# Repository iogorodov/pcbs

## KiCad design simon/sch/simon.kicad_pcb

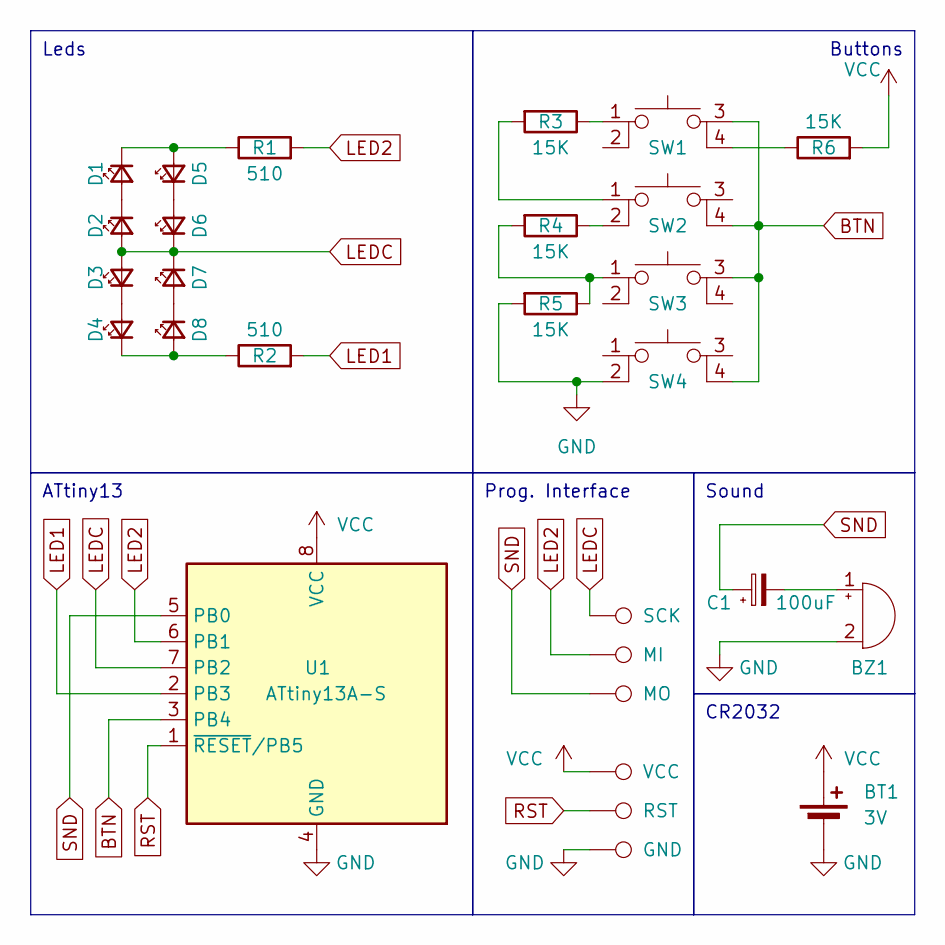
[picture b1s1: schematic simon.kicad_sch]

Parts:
BT1: 3V; BatteryHolder_KLS5_CR2032_02
BZ1: Buzzer; MagneticBuzzer_Kingstate_KCG0601
C1: 100uF; CP_Radial_D6.3mm_P2.50mm
D1, D2, D3, D4, D5, D6, D7, D8: LED_Small; LED_1206_3216Metric
R1, R2: 510; R_Axial_DIN0207_L6.3mm_D2.5mm_P7.62mm_Horizontal
R3, R4, R5, R6: 15K; R_Axial_DIN0207_L6.3mm_D2.5mm_P7.62mm_Horizontal
SW1, SW2, SW3, SW4: SW_Push_6x6mm
TP1: GND; TestPoint_Pad_D1.5mm
TP2: RST; TestPoint_Pad_D1.5mm
TP3: VCC; TestPoint_Pad_D1.5mm
TP4: SCK; TestPoint_Pad_D1.5mm
TP5: MI; TestPoint_Pad_D1.5mm
TP6: MO; TestPoint_Pad_D1.5mm
U1: ATtiny13A-S; SOIC-8W_5.3x5.3mm_P1.27mm

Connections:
BTN: SW1.3, SW2.4, SW3.3, SW4.4, U1.3 (PB4)
GND: BT1.2 (-), BZ1.2 (+), R5.2, SW4.2, TP1.1, U1.4 (GND)
LED1: R2.2, U1.2 (PB3)
LED2: R1.2, TP5.1, U1.6 (PB1)
LEDC: D2.2 (A), D3.2 (A), D6.1 (K), D7.1 (K), TP4.1, U1.7 (PB2)
unnamed: BZ1.1 (-), C1.2
unnamed: D1.2 (A), D2.1 (K)
unnamed: D1.1 (K), D5.2 (A), R1.1
unnamed: D3.1 (K), D4.2 (A)
unnamed: D4.1 (K), D8.2 (A), R2.1
unnamed: D5.1 (K), D6.2 (A)
unnamed: D7.2 (A), D8.1 (K)
unnamed: R3.1, SW1.1
unnamed: R3.2, SW2.1
unnamed: R4.1, SW2.2
unnamed: R4.2, R5.1, SW3.1
unnamed: R6.1, SW1.4
RST: TP2.1, U1.1 (~RESET/PB5)
SND: C1.1, TP6.1, U1.5 (PB0)
VCC: BT1.1 (+), R6.2, TP3.1, U1.8 (VCC)

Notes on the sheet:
Prog. Interface
Buttons
Sound
Leds
CR2032
ATtiny13

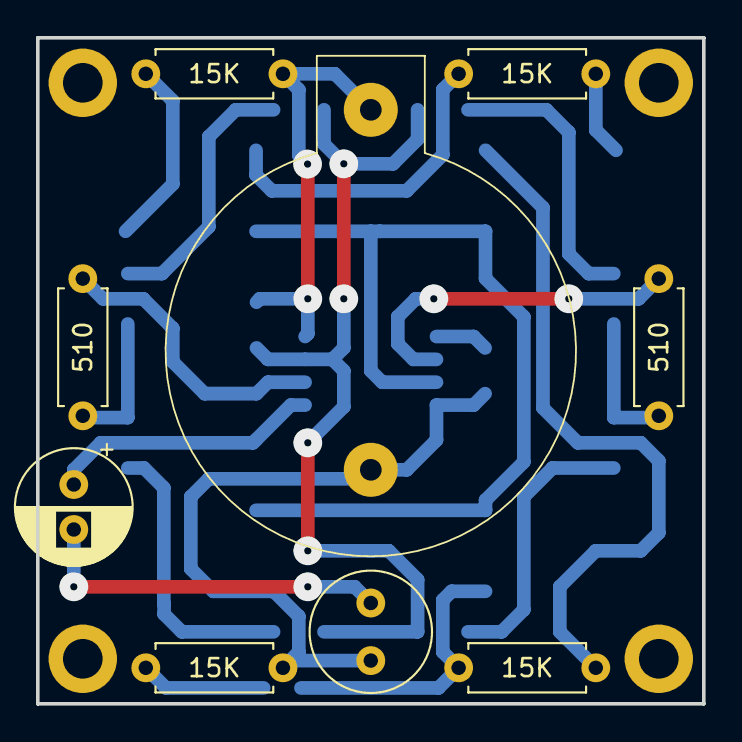
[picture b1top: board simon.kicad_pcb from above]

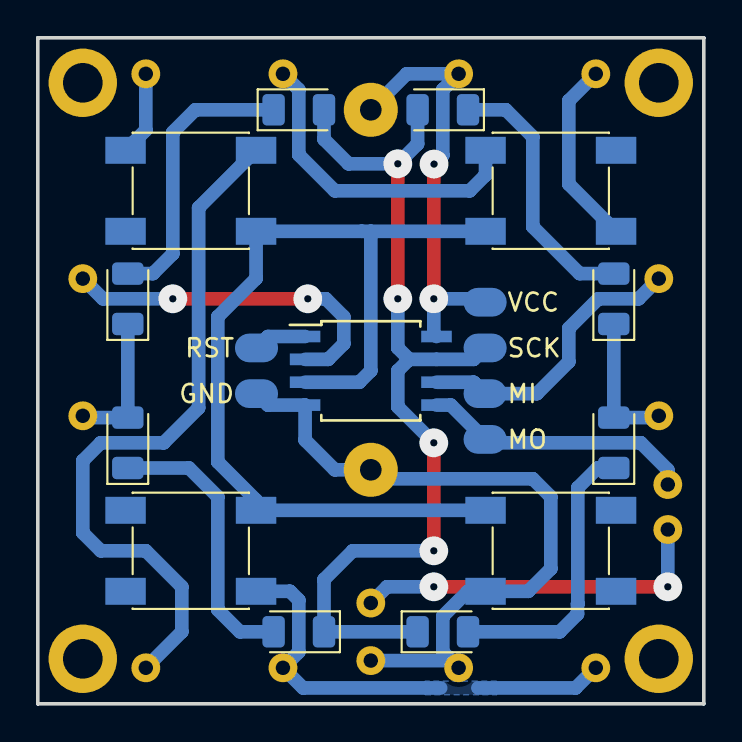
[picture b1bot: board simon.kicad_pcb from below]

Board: 2 copper layers, 37.0 x 37.0 mm, 28 parts (19 on the bottom side), 20 nets.

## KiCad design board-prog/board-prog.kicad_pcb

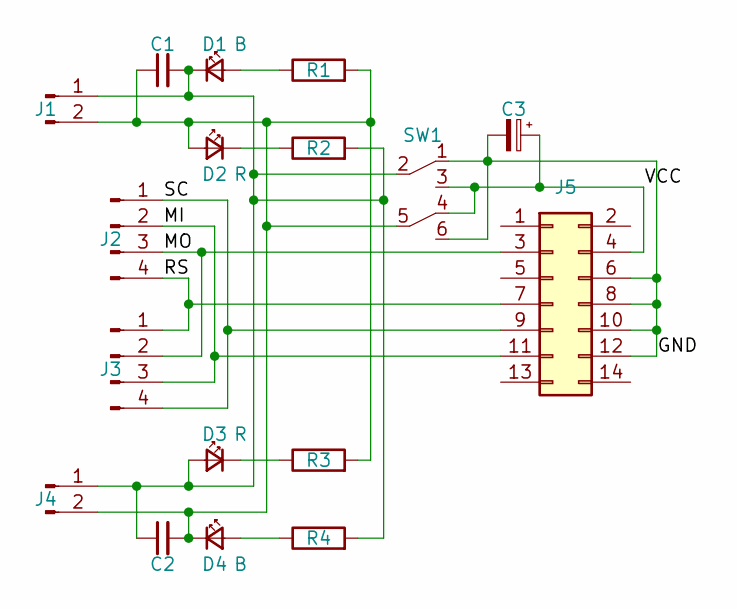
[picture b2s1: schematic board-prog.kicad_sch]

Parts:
C1, C2: 0.1uF; C_Disc_D5.0mm_W2.5mm_P2.50mm
C3: 100uF; CP_Radial_D8.0mm_P3.50mm
D1, D4: B; LED_1206_3216Metric_Pad1.42x1.75mm_HandSolder
D2, D3: R; LED_1206_3216Metric_Pad1.42x1.75mm_HandSolder
J1, J4: Conn_01x02_Pin; PinHeader_1x02_P2.54mm_Vertical
J2, J3: Conn_01x04_Pin; PinHeader_1x04_P2.54mm_Vertical
J5: Conn_02x07_Odd_Even; PinSocket_2x07_P2.54mm_Vertical
R1, R2, R3, R4: 5.1k; R_Axial_DIN0207_L6.3mm_D2.5mm_P7.62mm_Horizontal
SW1: SW_DPDT_MSS-22C02

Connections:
/GND: C3.2, J5.6, J5.8, J5.10, J5.12, SW1.1, SW1.6
/MI: J2.2, J3.3, J5.11
/MO: J2.3, J3.2, J5.3
/RS: J2.4, J3.1, J5.7
/SC: J2.1, J3.4, J5.9
/VCC: C3.1, J5.4, SW1.3, SW1.4
unnamed: D1.2 (A), R1.1
unnamed: C1.2, C2.1, D1.1 (K), D3.2 (A), J1.1, J4.1, R2.2, R4.2, SW1.2
unnamed: C1.1, C2.2, D2.2 (A), D4.1 (K), J1.2, J4.2, R1.2, R3.2, SW1.5
unnamed: D2.1 (K), R2.1
unnamed: D3.1 (K), R3.1
unnamed: D4.2 (A), R4.1

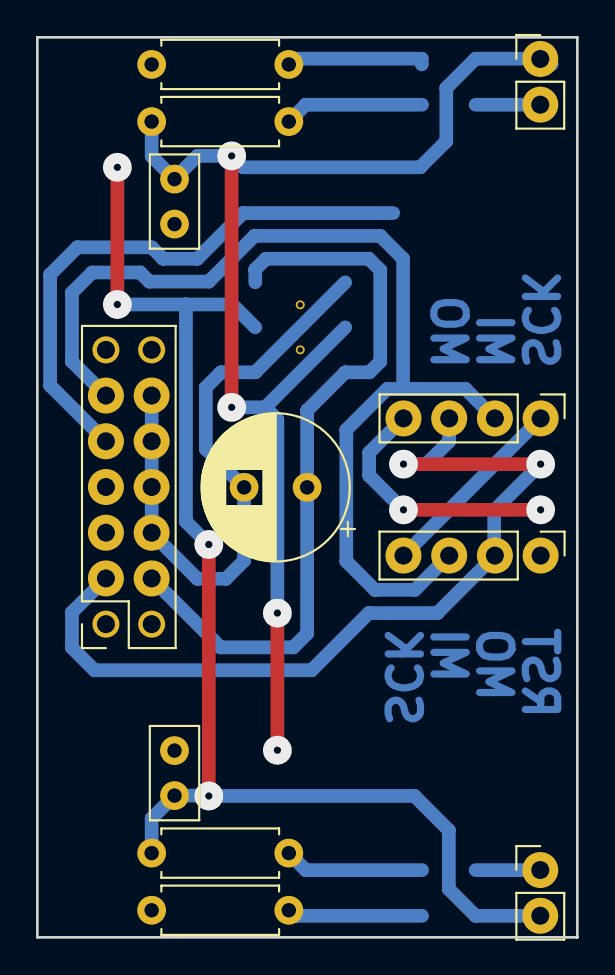
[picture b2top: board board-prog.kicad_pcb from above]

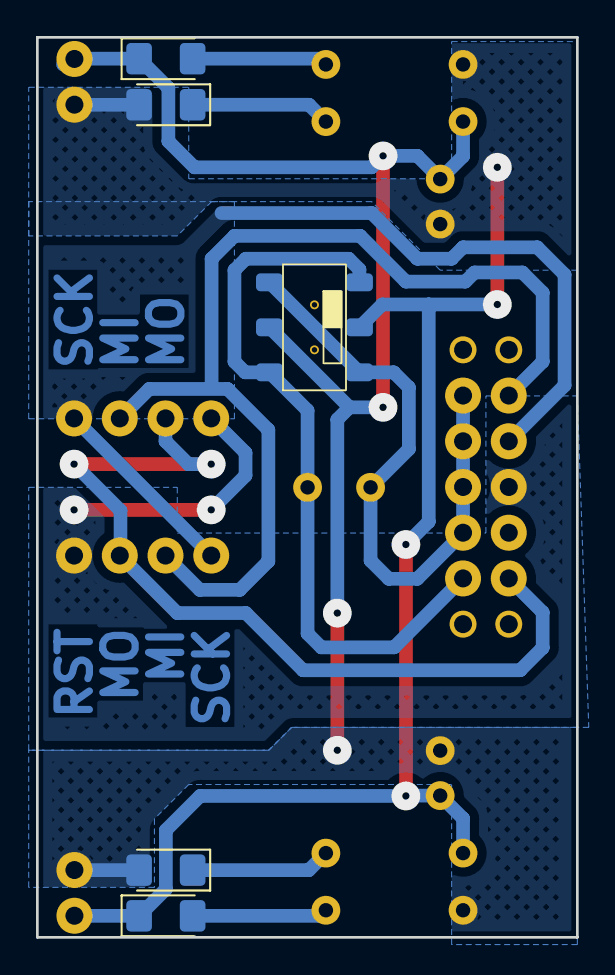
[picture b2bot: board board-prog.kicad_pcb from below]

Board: 2 copper layers, 30.0 x 50.0 mm, 17 parts (5 on the bottom side), 12 nets.

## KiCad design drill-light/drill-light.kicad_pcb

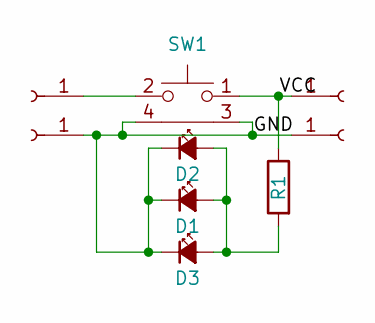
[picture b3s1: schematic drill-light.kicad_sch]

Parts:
D1, D2, D3: LED_Small_Filled; LED_D5.0mm_Clear
J1, J2, J3, J4: Conn_01x01_Socket; PinHeader_1x01_P2.54mm_Vertical
R1: R; R_Axial_DIN0207_L6.3mm_D2.5mm_P7.62mm_Horizontal
SW1: SW_Tactile_SPST_Angled_PTS645Vx31-2LFS

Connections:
/GND: D1.1 (K), D2.1 (K), D3.1 (K), J2.1, J3.1, SW1.3, SW1.4
/VCC: J1.1, R1.1, SW1.1
unnamed: D1.2 (A), D2.2 (A), D3.2 (A), R1.2
unnamed: J4.1, SW1.2

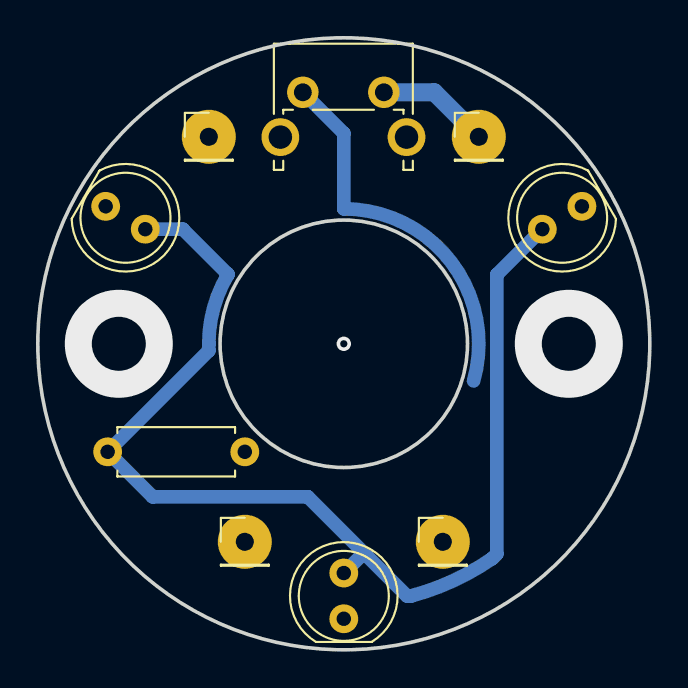
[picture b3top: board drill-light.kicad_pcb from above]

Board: 2 copper layers, 34.0 x 34.0 mm, 9 parts (0 on the bottom side), 4 nets.

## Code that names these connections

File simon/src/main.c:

#include <avr/io.h>
#include <avr/interrupt.h>
#include <avr/pgmspace.h>

uint16_t g_random = 0;

uint8_t getRandom() {
    for (uint8_t i = 0; i < 2; ++i) {
        uint8_t lsb = g_random & 1;
        g_random >>= 1;
        if (lsb || !g_random) {
            g_random ^= 0xb400;
        }
    }

    return g_random & 0xff;
}

uint8_t g_lastRandom4 = 0;

uint8_t getRandom4() {
    uint8_t value;
    do {
        value = (getRandom() & 0b00000011) + 1;
    } while (value == g_lastRandom4);
    g_lastRandom4 = value;
    return value;
}

const uint8_t LEDS[] PROGMEM = { 0, _BV(PB1) | _BV(PB4), _BV(PB3), _BV(PB1) | _BV(PB3), _BV(PB4) };

void led(uint8_t index) {
    PORTB = (PORTB & (0xff ^ (_BV(PB1) | _BV(PB3) | _BV(PB4)))) | pgm_read_byte_near(LEDS + index);
}

uint8_t g_buttonState = 0;

uint8_t getButtonsADC() {
    ADCSRA  = _BV(ADEN) | _BV(ADSC);
    while (ADCSRA & (1 << ADSC));
    const uint8_t value = ADCH;
    if (value > 224)
        return 0;
    if (value > 181)
        return 4;
    if (value > 149)
        return 3;
    if (value > 64)
        return 2;
    return 1;
}

uint8_t getButtonsPin() {
    const uint8_t button = PINB & _BV(PB2);

    if (!g_buttonState) {
        if (!button) {
            g_buttonState = 1;
            return 4;
        }
    } else if (button) {
        if (g_buttonState < 0b00010000) {
            g_buttonState = 0;
            return 1;
        }

        g_buttonState = 0;
    } else {
        if (g_buttonState & 0b00010000) {
            g_buttonState = 0b10000001;
            return 2;
        }

        if (!(g_buttonState & 0b10000000)) {
            g_buttonState += 2;
        }

        return 4;
    }

    return 0;
}

uint8_t getButtons() {
    if (ADCSRA & _BV(ADEN)) {
        return getButtonsADC();
    } else {
        return getButtonsPin();
    }
}

void setButtonsMode(uint8_t enable) {
    ADCSRA  = (enable << ADEN) | (enable << ADSC);
    DIDR0   = (enable << ADC1D);
}

volatile uint8_t g_tick = 0;

ISR(WDT_vect) {
    g_tick = 1;
}

void menu(uint8_t button);

uint8_t g_step = 0;
void(*g_stepFunc)(uint8_t) = menu;

void menu(uint8_t button) {
    getRandom();
    led(4 - g_step / 8);
}

int main()
{
    DDRB    = _BV(PB0) | _BV(PB1) | _BV(PB3) | _BV(PB4);

    ADMUX   = _BV(ADLAR) | _BV(MUX0);
    ADCSRA  = 0;
    ADCSRB  = 0;

    TCCR0A  = _BV(COM0A0) | _BV(WGM01) | _BV(WGM00);
    TCCR0B  = _BV(WGM02) | _BV(CS01);
    OCR0A   = 142;

    WDTCR   = _BV(WDTIE) | _BV(WDP0);

    sei();

    while (1) {
        while (!g_tick);
        g_stepFunc(getButtons());
        if (!g_step)
            g_step = 32;
        g_step--;
        g_tick = 0;
    }
}

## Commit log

2023-12-28 Use attiny project for attiny45
2024-02-09 Add code for simon game
2024-02-09 Add init state
2024-02-21 Update simon program
2024-02-21 Update simon logic
